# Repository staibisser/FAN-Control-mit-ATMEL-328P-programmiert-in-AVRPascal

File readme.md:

# FAN-Control – Lüfter- und Schiebersteuerung

> Kompakte Embedded-Steuerung für Lüfter und Abgasschieber eines Gasdurchlauferhitzers,
> entwickelt mit eigener Hardware in **KiCad** und Firmware in **AVRPascal** auf einem **ATmega328PB**.

---

## Überblick

**FAN-Control** überwacht den Betriebszustand eines Gasdurchlauferhitzers und steuert automatisch:

- den **Abgasschieber** (motorisch, via H-Brücke) – öffnet beim Einschalten des Geräts
- den **Lüfter** – schaltet temperaturabhängig zu

Die Steuerung erkennt den Gerätezustand über ein **Analogsignal**, misst die **Abgastemperatur** mit einem DS18B20-Sensor und reagiert zusätzlich auf einen **manuellen Taster**.

---

## Systemarchitektur

```
24 V DC
   │
   ▼
Spannungsaufbereitung
   │
   ▼
ATmega328PB (PD2–PD7)
   ├── PD3 ◄── LM358 (Analogsignal Gerätezustand)
   ├── PD4 ◄── DS18B20 (1-Wire Temperatursensor)
   ├── PD7 ◄── Taster (manuell Ein/Aus)
   ├── PD5/PD6 ──► DRV8871DDA (H-Brücke → Schieber-Motor)
   └── PD2 ──► AO3400A (MOSFET → Lüfter)
```

---

## Hardware

### Hauptkomponenten

| Bauteil             | Bezeichnung     | Funktion                              |
|---------------------|-----------------|---------------------------------------|
| Mikrocontroller     | ATmega328PB     | Zentrale Steuerlogik                  |
| Temperatursensor    | DS18B20         | 1-Wire Temperaturmessung              |
| Motortreiber        | DRV8871DDA      | H-Brücke für Schieber-Motor           |
| Lüftertreiber       | AO3400A         | N-Kanal MOSFET zum Schalten des Lüfters |
| Signalaufbereitung  | LM358           | Operationsverstärker für Geräte-Signal |
| Versorgung          | 24 V DC         | Externe Versorgungsspannung           |
| Gehäuse             | Bernic Series 350 | DIN-Schienenmontage               |

### Gehäuse

### Pin-Belegung (ATmega328PB)

| Pin  | Port | Richtung | Funktion                                    |
|------|------|----------|---------------------------------------------|
| PD2  | D2   | OUTPUT   | Lüfter Ein/Aus (via AO3400A MOSFET)         |
| PD3  | D3   | INPUT    | Betriebssignal Durchlauferhitzer (via LM358)|
| PD4  | D4   | I/O      | DS18B20 1-Wire Datenleitung                 |
| PD5  | D5   | OUTPUT   | DRV8871 IN1 – Motor Auf                     |
| PD6  | D6   | OUTPUT   | DRV8871 IN2 – Motor Zu                      |
| PD7  | D7   | INPUT    | Taster – manuell Schieber Ein/Aus           |

---

## Firmware

### Zustandslogik

Die Haupt-Schlaufe läuft kontinuierlich mit einer Pause von **250 ms** pro Zyklus.

```
┌─────────────────────────────────────────────────┐
<<<<<<< Updated upstream
│  Einschalten (SchieberOnOff = TRUE) wenn:       │
│    GEon = 1  (Durchlauferhitzer läuft)          │
│    OR  Temperatur > 40 °C                       │
│    OR  Taster aktiv                             │
├─────────────────────────────────────────────────┤
│  Ausschalten (SchieberOnOff = FALSE) wenn:      │
│    GEon = 0  AND  Temperatur ≤ 40 °C            │
│    AND  Taster nicht aktiv                      │
=======
│  Einschalten (SchieberOnOff = TRUE) wenn:        │
│    GEon = 1  (Durchlauferhitzer läuft)           │
│    OR  Temperatur > 40 °C                        │
│    OR  Taster aktiv                              │
├─────────────────────────────────────────────────┤
│  Ausschalten (SchieberOnOff = FALSE) wenn:       │
│    GEon = 0  AND  Temperatur ≤ 40 °C            │
│    AND  Taster nicht aktiv                       │
>>>>>>> Stashed changes
└─────────────────────────────────────────────────┘
```

**Temperatur-Schwellwert:** `TempFan = 40 °C` (konfigurierbar als Konstante im Quellcode)

**Fehlertoleranz:** Bei einem Lesefehler des DS18B20 (`seCRCError`, `seNoSensor`) bleibt der zuletzt gültige Temperaturwert (`lastGoodTemp`) erhalten.

### Motor-Ansteuerung

Der DRV8871-Motortreiber wird über zwei Ausgänge angesteuert:

| Befehl | IN1 | IN2 | Lüfter |
|--------|-----|-----|--------|
| Schieber AUF | HIGH | LOW | EIN |
| Schieber ZU  | LOW | HIGH | AUS |

Zwischen den Schaltzuständen werden kurze Mikrosekunden-Pausen eingehalten, um Stromspitzen zu vermeiden.

### DS18B20 – Eigene 1-Wire Implementierung

Der Sensor wird über **direktes Port-Bit-Banging** (DDRD / PORTD / PIND) ohne externe Bibliothek angesprochen. Die Implementierung beinhaltet:

- 1-Wire Reset mit Präsenzsignal-Erkennung
- Bit-genaues Read/Write mit µs-Timing
- **CRC8 Dallas-Prüfsumme** zur Datenvalidierung
- Fehlerbehandlung über den Typ `TSensorError`:

| Fehlercode     | Bedeutung                          |
|----------------|------------------------------------|
| `seNone`       | Kein Fehler                        |
| `seNoSensor`   | Sensor nicht erkannt (kein Präsenzsignal) |
| `seCRCError`   | Prüfsummenfehler                   |
| `seOutOfRange` | Temperaturwert ausserhalb −55…+125 °C |

---

## Projektstruktur

```
FAN-Control-mit-ATMEL-328P-programmiert-in-AVRPascal/
├── Hardware/
│   ├── 700000008-SCHIEBER-V3.kicad_sch   # Schaltplan
│   ├── 700000008-SCHIEBER-V3.kicad_pcb   # PCB-Layout
│   └── 700000008-SCHIEBER-V3.kicad_pro   # KiCad Projektdatei
│
├── Software/
│   ├── P_700000008_V3_A.pas              # Hauptprogramm
│   ├── DS18B20.pas                       # 1-Wire Sensor Unit
<<<<<<< Updated upstream
│   ├── testDS18B20.pas                   # 1-Wire Sensor Test mit Ausgabe an UART
=======
│   ├── P_700000008_V3_A.hex              # Flash-fertige Hex-Datei
│   ├── P_700000008_V3_A.elf              # ELF Debug-Binary
│   └── P_700000008_V3_A.bin              # Rohes Binärimage
>>>>>>> Stashed changes
│
├── images/
│   ├── render.jpg                        # PCB 3D-Render
│   └── bernicSeries350.jpg               # Gehäuse DIN-Schiene
│
├── LICENSE
└── readme.md
```

---

## Voraussetzungen

### Hardware

- Zielhardware mit **ATmega328PB**
- 24 V DC Versorgung
- DS18B20 Temperatursensor
- Abgasschieber mit geeignetem DC-Motor
- Lüfter
- Programmer: **USBasp** oder kompatibel

### Software

- [AVRPascal / Free Pascal AVR Toolchain](https://www.freepascal.org/)
- [avrdude](https://github.com/avrdudes/avrdude) zum Flashen
- [KiCad](https://www.kicad.org/) für Änderungen an der Hardware

---

## Build & Flash

### Flashen (fertige Hex-Datei)

```bash
avrdude -c usbasp -p m328pb -P usb -U flash:w:Software/P_700000008_V3_A.hex
```

> **Hinweis:** Den Partcode `-p m328pb` verwenden (nicht `m328p`), da es sich um den **ATmega328PB** handelt.

### Fuse-Konfiguration

Die Fuse-Bits müssen zur Taktquelle passen:

| Fuse   | Empfehlung                        |
|--------|-----------------------------------|
| CKSEL  | Externer 16 MHz Quarz             |
| CKDIV8 | Deaktiviert (kein Vorteiler)      |
| BODLEVEL | Je nach Anwendung (empfohlen: 2,7 V) |

Beispiel (externer 16 MHz Quarz, BOD 2,7 V):

```bash
avrdude -c usbasp -p m328pb -P usb \
  -U lfuse:w:0xFF:m \
  -U hfuse:w:0xD9:m \
  -U efuse:w:0xFF:m
```

> ⚠️ Falsche Fuse-Einstellungen können den Mikrocontroller scheinbar unbrauchbar machen. Vor dem Setzen unbedingt mit dem Datenblatt abgleichen.

---

## Projektstatus

| Bereich      | Status          |
|--------------|-----------------|
| Hardware     | ✅ Entwickelt    |
| Firmware     | ✅ Lauffähig     |
| Taktquelle   | ✅ Externer 16 MHz Quarz getestet |
| Flash-Prozess | ✅ USBasp / avrdude erfolgreich |
| Feldbetrieb  | 🔄 In Erprobung |

---

## Mögliche Erweiterungen

- Serielle Diagnoseausgabe (UART) für Temperatur- und Zustandslogs
- Fehlererkennung mit Status-LED oder Summerton
- Parametrierung von `TempFan` über Taster oder EEPROM
- Watchdog-Timer für erhöhte Ausfallsicherheit
- Stückliste (BOM) als PDF oder CSV

---

## Sicherheitshinweis

Dieses Projekt ist **kein zertifiziertes Sicherheitsprodukt** und **kein freigegebenes Seriengerät**.
Der Einsatz erfolgt ausschliesslich auf eigene Verantwortung – insbesondere bei Anwendungen mit
Gasgeräten, Wärmequellen oder beweglichen Aktoren. Vor dem Praxiseinsatz müssen alle
elektrischen, thermischen und sicherheitstechnischen Aspekte eigenständig geprüft werden.

---

## Lizenz

MIT License – siehe [LICENSE](LICENSE)

---

<<<<<<< Updated upstream
=======
## Autor

**Christof Biner** ([@staibisser](https://github.com/staibisser))
>>>>>>> Stashed changes

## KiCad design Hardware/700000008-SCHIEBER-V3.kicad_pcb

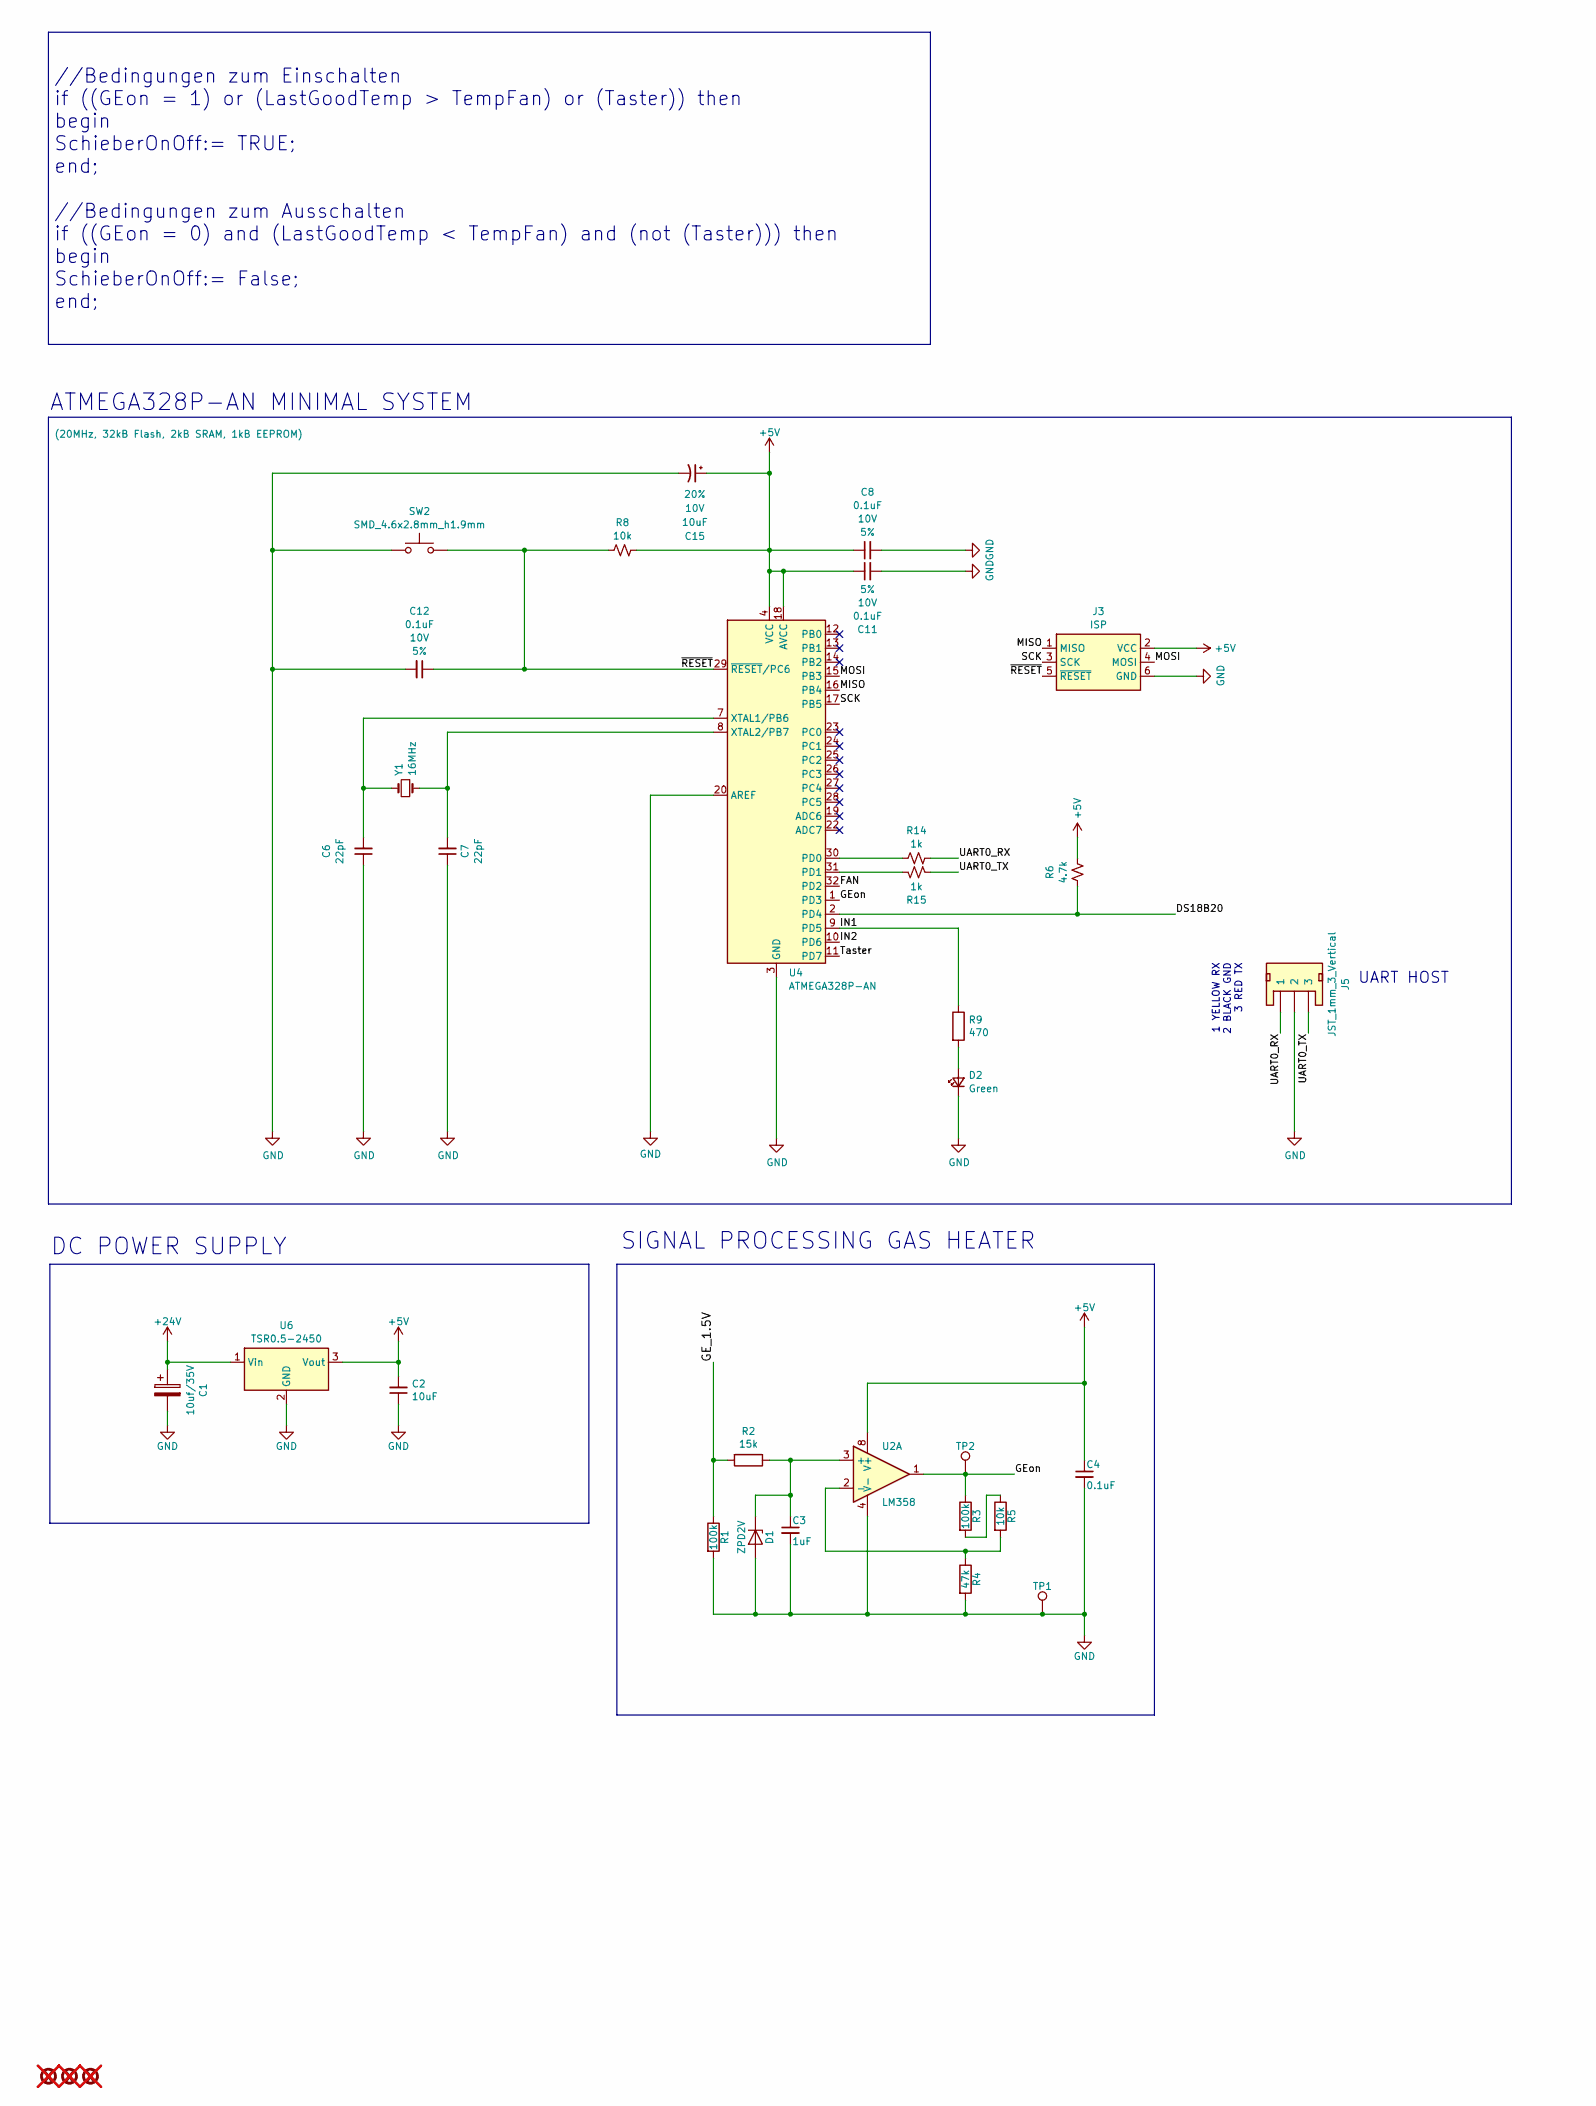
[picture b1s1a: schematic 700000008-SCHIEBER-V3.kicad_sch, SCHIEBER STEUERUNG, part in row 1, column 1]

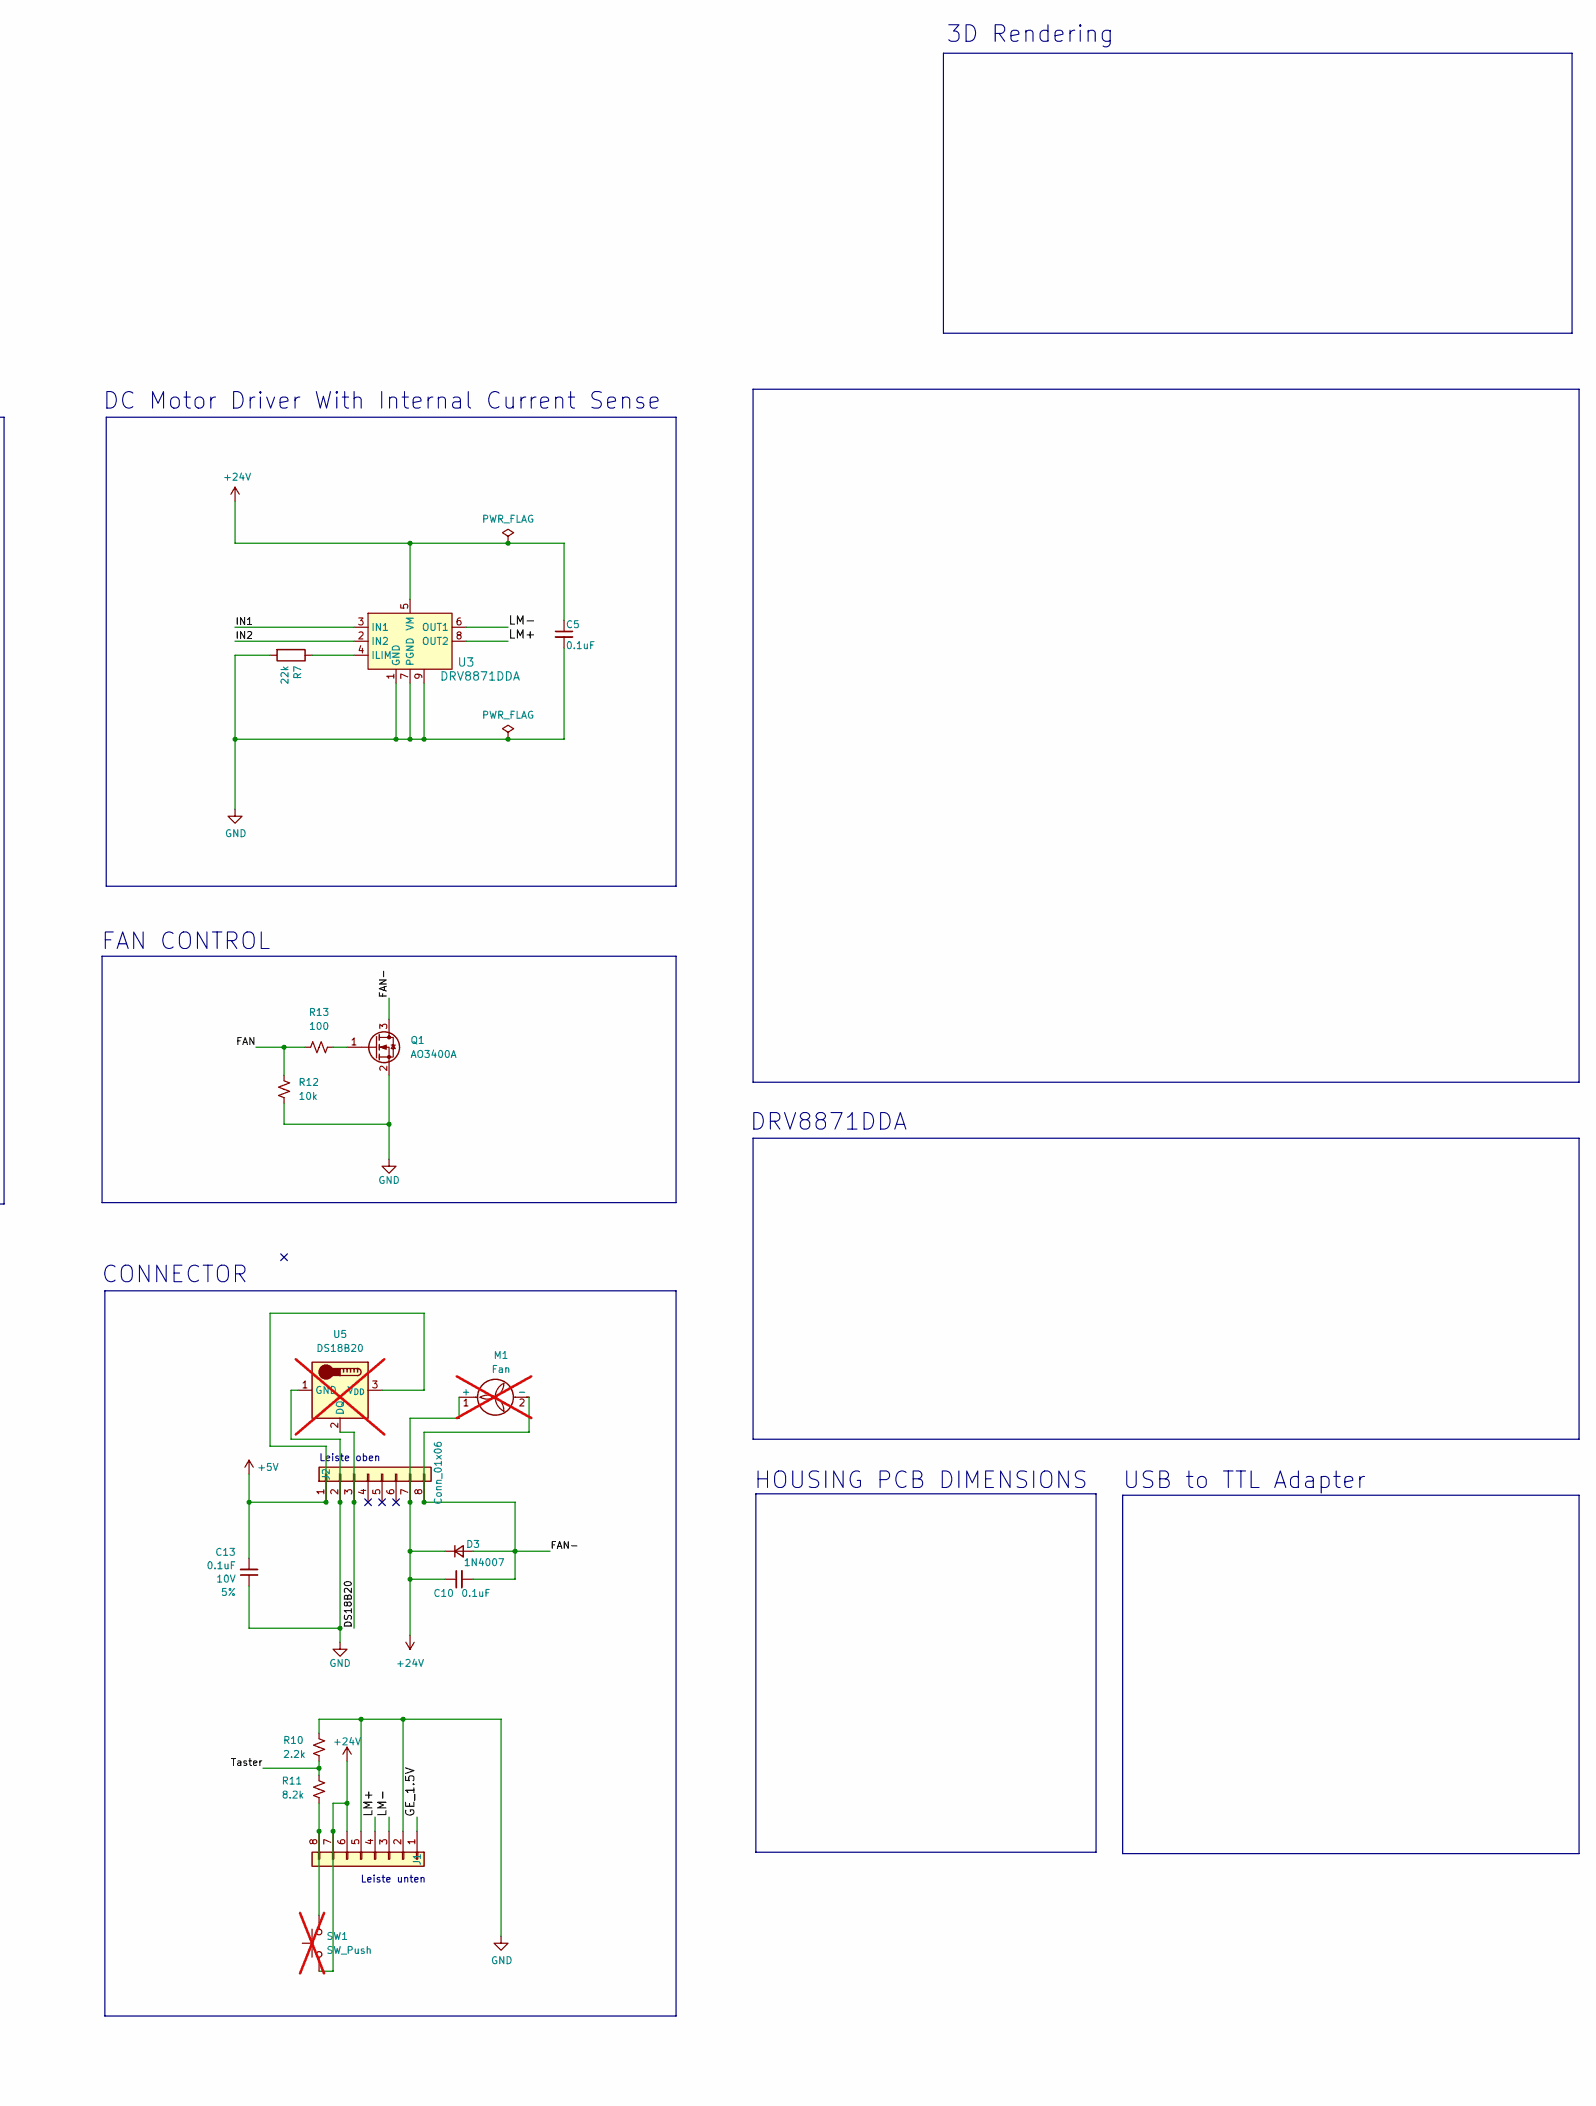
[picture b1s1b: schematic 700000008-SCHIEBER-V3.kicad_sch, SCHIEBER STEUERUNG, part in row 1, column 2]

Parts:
C1: 10uf/35V; CP_Elec_4x5.8; Tolerance 20%; Voltage 35V; MPN EXV106M035A9DAA; Digikey EXV106M016S9BAA
C2: 10uF; C_0603_1608Metric; Tolerance 20%; Voltage 10V
C3: 1uF; C_0603_1608Metric; Tolerance 5%
C4, C5: 0.1uF; C_0603_1608Metric; Tolerance 5%; Voltage 10V
C6, C7: 22pF; C_0402_1005Metric; Voltage 10V; Tolerance 5%
C8, C10, C11, C12, C13: 0.1uF; C_0603_1608Metric; Voltage 10V; Tolerance 5%
C15: 10uF; C_0603_1608Metric; Voltage 10V; Tolerance 20%
D1: ZPD2V; D_SOD-123; MPN BZT52C2V0-7-F; Digikey BZT52C2V0-7-F
D2: Green; LED_1206_3216Metric_Green; MPN IN-S126ATG; Digikey IN-S126ATG
D3: 1N4007; SOD-123; Voltage 1000V; MPN 1N4007W; Digikey 1N4007W
FID1, FID2, FID3: Fiducial_0.5mm; Fiducial_0.5mm_Mask1mm; not fitted
J1, J2: Conn_01x06; TerminalBlock_Phoenix_PT-1,5-8-3.5-H_1x08_P3.50mm_Horizontal; MPN 1751303; Digikey 1751303
J3: ISP; PinHeader_2x03_P1.27mm_Vertical; MPN 20021111-00006T1LF
J5: JST_1mm_3_Vertical; JST_1x03_P1.0mm_Vertical_SMD; MPN BM03B-SRSS-TB
M1: Fan; not fitted
Q1: AO3400A; SOT-23; MPN AO3400A
R1, R3: 100k; R_0603_1608Metric; Tolerance 5%
R2: 15k; R_0603_1608Metric; Tolerance 5%
R4: 47k; R_0603_1608Metric; Tolerance 5%
R5, R8, R12: 10k; R_0603_1608Metric; Tolerance 5%
R6: 4.7k; R_0603_1608Metric; Tolerance 5%
R7: 22k; R_0603_1608Metric; Tolerance 5%
R9: 470; R_0603_1608Metric; Tolerance 5%
R10: 2.2k; R_0603_1608Metric; Tolerance 5%
R11: 8.2k; R_0603_1608Metric; Tolerance 5%
R13: 100; R_0603_1608Metric; Tolerance 5%
R14, R15: 1k; R_0603_1608Metric; Tolerance 5%
SW1: SW_Push; not fitted
SW2: SMD_4.6x2.8mm_h1.9mm; Push_SMD_4.6x2.8mm_h1.9mm; MPN KMR221GLFS; Digikey CKN10259CT-ND
TP1, TP2: 1.0mm; TestPoint_THTPad_D2.0mm_Drill1.0mm; MPN 5000; Digikey 36-5000-ND
U2: LM358; SOIC-8_W3.9mm; MPN LM358DT; Digikey 497-1591-1-ND
U3: DRV8871DDA; SOIC-8-1EP_3.9x4.9mm_P1.27mm_EP2.41x3.81mm_ThermalVias; MPN DRV8871DDA; Digikey 296-44509-5-ND
U4: ATMEGA328P-AN; TQFP-32_7x7mm_P0.8mm; MPN ATMEGA328P-AN
U5: DS18B20; TO-92_Inline; not fitted
U6: TSR0.5-2450; Converter_DCDC_TRACO_TSR0.5-24xx_TSR0.5-24xxx_THT; MPN TSR 0.5-2450; Digi-Key_PN 1951-TSR0.5-2450-ND
Y1: 16MHz; Crystal_SMD_2.0x1.6mm; MPN XRCGB16M000FXN01R0

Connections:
+5V: C2.2, C4.1, C8.1, C11.1, C13.2, C15.1, J2.1, J3.2 (VCC), R6.2, R8.2, U2.8 (V+), U4.4 (VCC), U4.6 (VCC), U4.18 (AVCC), U5.3 (V_{DD}), U6.3 (Vout)
+24V: C1.1, C5.1, C10.1, D3.1 (K), J1.6, J1.7, J2.7, M1.1 (+), SW1.1, U3.5 (VM), U6.1 (Vin)
/DS18B20: J2.3, R6.1, U4.2 (PD4), U5.2 (DQ)
/FAN: R12.1, R13.1, U4.32 (PD2)
/FAN-: C10.2, D3.2 (A), J2.8, M1.2 (-), Q1.3 (D)
/GE_1.5V: J1.1, R1.1, R2.2
/GEon: R3.1, TP2.1, U2.1, U4.1 (PD3)
/IN1: R9.1, U3.3 (IN1), U4.9 (PD5)
/IN2: U3.2 (IN2), U4.10 (PD6)
/LM+: J1.4, U3.8 (OUT2)
/LM-: J1.3, U3.6 (OUT1)
/MISO: J3.1 (MISO), U4.16 (PB4)
/MOSI: J3.4 (MOSI), U4.15 (PB3)
/SCK: J3.3 (SCK), U4.17 (PB5)
/Taster: R10.1, R11.2, U4.11 (PD7)
/UART0_RX: J5.1, R14.2
/UART0_TX: J5.3, R15.2
/~RESET: C12.1, J3.5 (~RESET), R8.1, SW2.2, U4.29 (~RESET/PC6)
GND: C1.2, C2.1, C3.2, C4.2, C5.2, C6.1, C7.1, C8.2, C11.2, C12.2, C13.1, C15.2, D1.2 (A), D2.1 (K), J1.2, J1.5, J2.2, J3.6 (GND), J5.2, Q1.2 (S), R1.2, R4.2, R7.2, R10.2, R12.2, SW2.1, TP1.1, U2.4 (V-), U3.1 (GND), U3.7 (PGND), U3.9, U4.3 (GND), U4.5 (GND), U4.20 (AREF), U4.21 (GND), U5.1 (GND), U6.2 (GND)
unnamed: C3.1, D1.1 (K), R2.1, U2.3 (+)
unnamed: D2.2 (A), R9.2
unnamed: J1.8, R11.1, SW1.2
unnamed: Q1.1 (G), R13.2
unnamed: R3.2, R5.1
unnamed: R4.1, R5.2, U2.2 (-)
unnamed: R7.1, U3.4 (ILIM)
unnamed: R14.1, U4.30 (PD0)
unnamed: R15.1, U4.31 (PD1)
unnamed: C6.2, U4.7 (XTAL1/PB6), Y1.2
unnamed: C7.2, U4.8 (XTAL2/PB7), Y1.1

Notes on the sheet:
CONNECTOR
ATMEGA328P-AN MINIMAL SYSTEM
USB to TTL Adapter
UART HOST
1 YELLOW RX 2 BLACK GND 3 RED TX
DRV8871DDA
3D Rendering
DC POWER SUPPLY
FAN CONTROL
HOUSING PCB DIMENSIONS
Leiste oben
Leiste unten
SIGNAL PROCESSING GAS HEATER
DC Motor Driver With Internal Current Sense
//Bedingungen zum Einschalten if ((GEon = 1) or (LastGoodTemp > TempFan) or (Taster)) then begin SchieberOnOff:= TRUE; end; //Bedingungen zum Ausschalten if ((GEon = 0) and (LastGoodTemp < TempFan) and (not (Taster))) then begin SchieberOnOff:= False; end;

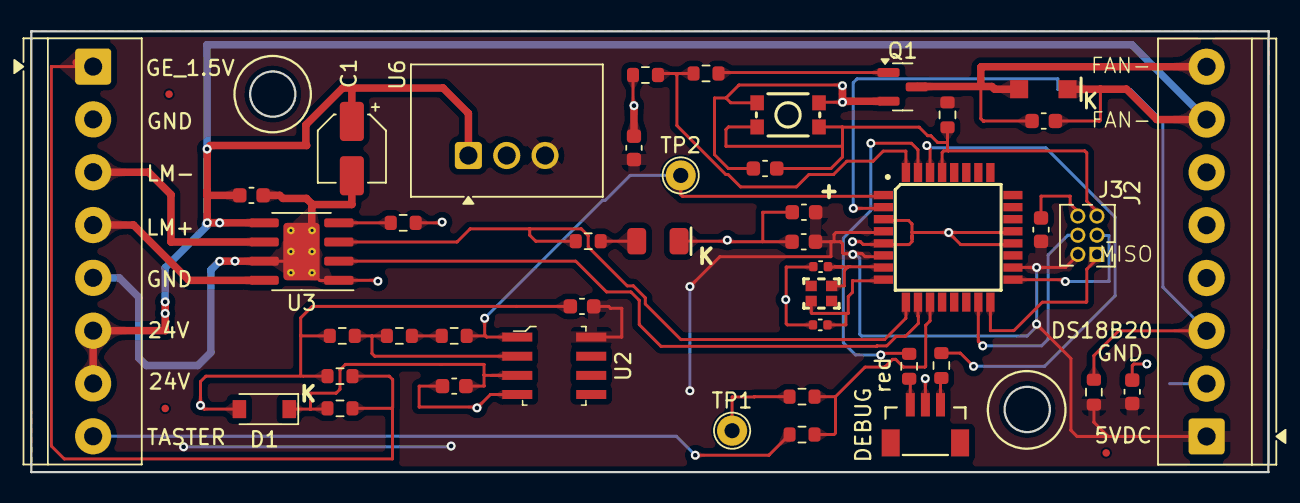
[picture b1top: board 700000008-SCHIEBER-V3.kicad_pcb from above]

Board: 2 copper layers, 82.0 x 29.2 mm, 47 parts (0 on the bottom side), 30 nets.

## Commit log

2026-03-28 intial commit
2026-03-28 clean
2026-03-28 readme ergänzt
2026-03-28 tips angepasst
    Removed GitHub tips section from the readme.
2026-03-28 Update images in READMEbilder
    Replaced images in the README with updated versions and removed old images.
2026-03-28 Clean up README
2026-03-28 Revise README
    Updated project structure and software toolchain details in README.
2026-03-30 ds18b20 test
2026-03-30 URAT TEST
2026-03-30 clean *.hex
2026-03-30 clean *.elf *.bin, *.hex
2026-03-30 Korrektur Beispiel, Kopier Fehler

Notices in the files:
Hardware/700000008-SCHIEBER-V3.kicad_pcb:
License: MIT (siehe LICENSE im Repository)
